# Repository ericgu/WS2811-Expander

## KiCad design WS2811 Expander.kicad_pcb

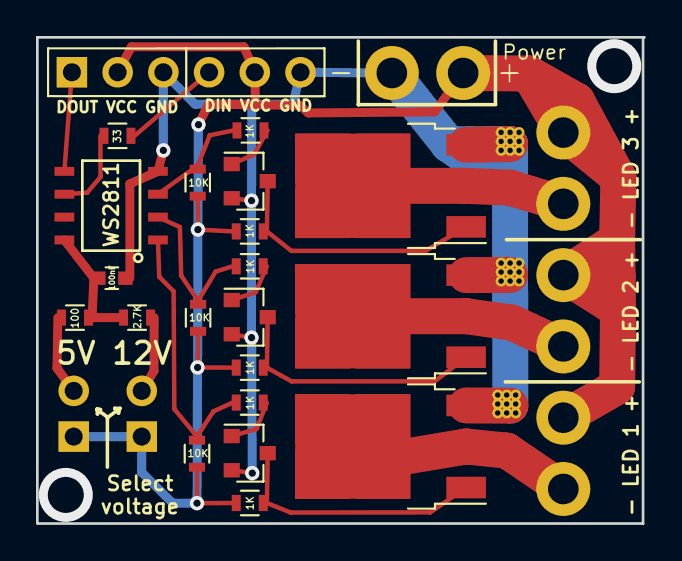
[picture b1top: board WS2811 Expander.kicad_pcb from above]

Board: 2 copper layers, 33.7 x 27.0 mm, 25 parts (0 on the bottom side), 17 nets.

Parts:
 R10: 0; Pin_Header_Straight_1x02_Pitch2.54mm
C1 : 100nF; C_0603
J1 : Molex__KK-396-02_02x3.96mm_Straight
J2 : Molex_KK-6410-06_06x2.54mm_Straight
J3: Pin_Header_Straight_1x06_Pitch2.54mm
Q1 , Q3 , Q4 : MMBT3904; SOT-23
Q2, Q5, Q6: IRLR7821PBF; TO-252-3_TabPin4
R1, R2, R3: 1K; R_0603
R4 , R5 , R6 , R12, R13, R14: 10K; R_0603
R7 : 100; R_0603
R8 : 2.7K; R_0603
R9 : 0; Pin_Header_Straight_1x02_Pitch2.54mm
R11 : 33; R_0603
U1: WS2811; SOP-8

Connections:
/DIN: J3.4, R11.2
/DOUT: J3.1, U1.5
/GND: C1.2, J1.2, J3.3, J3.6, Q1.2, Q2.3, Q3.2, Q4.2, Q5.3, Q6.3, U1.4
/OUTB: R3.2, R14.2, U1.3
/OUTG: R2.2, R13.2, U1.2
/OUTR: R1.2, R12.2, U1.1
/VCC: R10.1, J1.1, J2.2, J2.4, J2.6, J3.2, J3.5, R4.1, R5.1, R6.1, R9.1, R12.1, R13.1, R14.1
unnamed: C1.1, R7.2, R8.2, U1.8
unnamed: Q1.1, R1.1
unnamed: Q1.3, Q2.1, R4.2
unnamed: Q3.1, R2.1
unnamed: Q3.3, Q5.1, R5.2
unnamed: Q4.1, R3.1
unnamed: Q4.3, Q6.1, R6.2
unnamed: R7.1, R9.2
unnamed: R10.2, R8.1
unnamed: R11.1, U1.6

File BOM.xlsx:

WS2811 expander BOM
 |  |  | Price |  | Total |  |  |  |  |  |  |  |  | allpcb assembled
Count | Part | Package | US Best | China | US Best | China
1 | PC Board |  | 0.38 | 0.38 | 0.38 | 0.38 | allpcb
1 | WS2811 | SOP-8 | 0.06 | 0.06 | 0.06 | 0.06 | arrow |  |  |  |  |  |  | 5.96E-2 | 5.96E-2
3 | IRLR7821PBF MOSFET | TO-252-3, DPAK | 0.44 | 0.15 | 1.32 | 0.44999999999999996 | arrow |  |  |  |  |  |  | 0.35 | 1.0499999999999998
3 | MMBT3904 NPN transistor | SOT-23 | 0.03 | 0.01 | 0.09 | 0.03 | arrow |  |  |  |  |  |  | 1.4800000000000001E-2 | 4.4400000000000002E-2
1 | 100nF capacitor | SMD 0805 | 0.08 | 0.01 | 0.08 | 0.01 | ebay |  |  |  |  |  |  | 1.78E-2 | 1.78E-2
1 | 33 ohm resistor | SMD 0805 | 0.01 | 0.01 | 0.01 | 0.01 | arrow |  |  |  |  |  |  | 2.7000000000000001E-3 | 2.7000000000000001E-3
1 | 100 ohm resistor | SMD 0805 | 0.01 | 0.01 | 0.01 | 0.01 | arrow |  |  |  |  |  |  | 2.7000000000000001E-3 | 2.7000000000000001E-3
1 | 2.7 K resistor | SMD 0805 | 0.01 | 0.01 | 0.01 | 0.01 | arrow |  |  |  |  |  |  | 2.7000000000000001E-3 | 2.7000000000000001E-3
6 | 10K resistor | SMD 0805 | 0.01 | 0.01 | 0.06 | 0.06 | arrow |  |  |  |  |  |  | 2.7000000000000001E-3 | 1.6199999999999999E-2
3 | 1K resistor | SMD 0805 | 0.01 | 0.01 | 0.03 | 0.03 | arrow |  |  |  |  |  |  | 2.7000000000000001E-3 | 8.0999999999999996E-3
 |  |  |  |  | 2.0499999999999998 | 1.05 | arrow |  |  |  |  |  |  |  | 1.2041999999999997
 |  |  |  |  |  |  |  |  |  |  | Joints | 52 | 1.5E-3 |  | 7.8E-2
1 | 6 pin 3.96mm header |  | 0.38 | 0.1 | 0.38 | 0.1
1 | 2 pin 3.96mm header |  | 0.14000000000000001 | 0.03 | 0.14000000000000001 | 0.03 |  |  |  |  |  |  |  |  | 1.2821999999999998
1 | 6 pin 2.54 mm header |  | 0.15 | 0.03 | 0.15 | 0.03
 |  |  |  |  | 0.67 | 0.16
 |  |  |  |  |  |  |  |  |  |  | Qty | 1000 |  |  | 1282.1999999999998
 |  |  |  |  |  |  |  |  |  |  | Setup | 7 |  |  | 7
Sources |  |  |  |  | 2.7199999999999998 | 1.21 |  |  |  |  | Extended | 3 |  |  | 3
PC board |  |  | Each |  |  |  |  |  |  |  | Stencil | 1.5 |  |  | 1.5
 | jlcpcb | 10@$7.24, 25@14.77 | 0.59 |  |  |  |  |  |  |  |  |  |  |  | 1293.6999999999998 |  | 1.2936999999999999
WS2811
 | aliexpress, Chinese manufacturer's store | 50@$2.85 | 0.06
IRLR7821 |  |  |  |  | end of life, IRF7821TRPBF is the updated version.
 | ae, xina (clone) | 30@$11.29 | 0.38 |  |  |  |  | board total |  |  | Boards | Assembly | Each | Total
 | ae, maysin (clone) | 100@$14.50 | 0.15 |  |  |  |  | 5 |  | 10 | 0.5 | 2.4300000000000002 | 2.93 | 29.3
 | Digikey | 10@$9.45 | 0.95 |  |  |  |  | 5.6 |  | 25 | 0.22399999999999998 | 1.74 | 1.964 | 49.1
 | Arrow | 10@$4.40, 100@38.37 | 0.44 |  | (obsolete version) |  |  | 12.1 |  | 100 | 0.121 | 1.4 | 1.5209999999999999 | 152.1
 |  |  |  |  |  |  |  | 28.2 |  | 500 | 5.6399999999999999E-2 | 1.31 | 1.3664000000000001 | 683.2
mmbt3904 |  |  |  |  |  |  |  | 48.4 |  | 1000 | 4.8399999999999999E-2 | 1.29 | 1.3384 | 1338.4
 | Mouser |  | 0.11
 | Arrow |  | 0.03
 | ae, Yunyida | 100@$1.40 | 0.01
100nF
 | ae, Yunyida | 200@$1.35 | 5.0000000000000001E-3
 | Mouser |  | 0.08
 | Digikey |  | 0.1
0805 res | ae, various | 100@$0.70 | 0.01
 | Digikey | 1@$0.10, 10@$0.83, 100@$3.18 | 0.03
 | Arrow | 1@$0.10, 10@$0.12, | 0.01
 |  | 25@$0.25, 100@$1.04
3.96 mm header, 6 pin
 | digikey | 10 | 0.38
 | ae |  | 0.1
3.96mm header, 2 pin
 | digikey | 10 | 0.14000000000000001
 |  |  | 0.03
2.54mm header, 6 pin
 | digikey | 10 | 0.15
 | ae, gold |  | 0.03
 | ae, silver |  | 0.01

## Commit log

2019-07-30 Production version
2020-05-25 updated design, new test app, ready for assembly
